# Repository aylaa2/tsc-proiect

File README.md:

# OpenBook – Open-Source E-Book Reader

OpenBook este un e-book reader open-source, low-cost, dezvoltat în cadrul proiectului TSC.  
Dispozitivul este construit pe baza microcontrolerului **ESP32-C6** și integrează funcționalități avansate de afișare, comunicație și consum redus de energie, fiind pregătit pentru producție în masă.

---

##  Diagrama Bloc

Diagrama bloc care ilustrează conexiunile dintre toate componentele:

---

##  BOM – Bill of Materials

# Bill of Materials (BOM)

| Package | Parts | Datasheet | 
|:--------|:------|:----------|
| ADAFRUIT_CHIP-LED0603 | CHG_LED | [Link](https://www.snapeda.com/parts/KP-1608SURCK/Kingbright/view-part/?ref=search&t=LED%200603) | 
| SJ | SJ1 | [Link](https://grabcad.com/library/solder-jumpers-1) |
| ESP32_WROVER_EAGLE-LTSPICE_R0402 | R1_PWRUSB, R1, R1_PINH1, R2-PINH, R2-PINH1, R5, R6, R7, R8, R9, R10, R_BOOT, R_CL1, R_RESET, R3, R1_PINH, R4, R_CHANGE, R_CAPACITOR, R2, R1_BAT, R2_BAT, R2_USB, R2_USB1 | [Link](https://componentsearchengine.com/part-view/R0402%201%25%20100%20K%20(RC0402FR-07100KL)/YAGEO) | 
| ESP32_WROVER_EAGLE-LTSPICE_C0402 | C1, C2, C4_USB, C6, C8, C9, C10, C_DELAY, EPD_C5, EPD_C1, EPD_C2, EPD_C6, EPD_C7, EPD_C8, EPD_C9, EPD_C10, EPD_C11, EPD_C12, C7, C5, C4, C1_BAT, C1_BAT1, C1_BAT2, C2_BAT, C5_USB | [Link](https://componentsearchengine.com/part-view/CC0402MRX5R5BB106/YAGEO) | 
| RCL_CT3528 | C3 | [Link](https://stud33302.autodesk360.com/g/shares/SH30dd5QT870c25f12fc6065d74bcaa3bf24) |
| 112ATAARR03ATTEND | J4 | [Link](Link) |
| ESP32_WROVER_SPARKFUN-DISCRETESEMI_SOT23-3 | Q1, Q2 | [Link](https://ro.mouser.com/ProductDetail/Microchip-Technology/MCP73831T-5ACI-OT?qs=hH%252BOa0VZEiAcgAcEkuamXg%3D%3D) |
| SOT95P280X125-5N | IC1 | [Link](https://componentsearchengine.com/part-view/BD5229G-TR/ROHM%20Semiconductor) |
| MYBUTTON | BOOT_BUTTON, CHANGE_BUTTON, RESET_BUTTON | [Link](https://industry.panasonic.com/global/en/products/control/switch/light-touch/number/evqpuj02k) |
| CAPCP3225X100N | C10_SUPERCAP | [Link](https://www.snapeda.com/parts/CPH3225A/Seiko+Instruments/view-part/?ref=eda) | 
| SOIC127P1032X265-16N | U3 | [Link](https://www.snapeda.com/parts/DS3231SN%23/Analog+Devices/view-part/?ref=eda) | 
| XCVR_ESP32-C6-WROOM-1-N8 | U2 | [Link](https://www.snapeda.com/parts/ESP32-C6-WROOM-1-N8/Espressif+Systems/view-part/?ref=eda) | 
| ESP32C6_VARISTOR_CT/CN1812 | PFMF.050.1 | [Link](Link) | 
| ESP32_WROVER_AVX---SD0805S020S1R0_AVX_SD0805S020S1R0_0 | D2, D7 | [Link](https://eu.mouser.com/ProductDetail/KYOCERA-AVX/SD0805S020S1R0?qs=jCA%252BPfw4LHbpkAoSnwrdjw%3D%3D) | 
| ESP32_WROVER_BME680_PSON80P300X300X100-8N | SENSOR2 | [Link](https://www.snapeda.com/parts/BME680/Bosch/view-part/?welcome=home) | 
| ESP32_WROVER_SPARKFUN-IC-POWER_SOT23-5 | U0 | [Link](Link) |
| FH34SRJ24S05SH99 | J1 | [Link](Link) | 
| SON50P200X200X80-9N | U4 | [Link](https://www.snapeda.com/parts/MAX17048G+T10/Analog+Devices/view-part/?ref=eda) | 
| SOD3716X135N | D3, D4, D5 | [Link](Lihttps://eu.mouser.com/ProductDetail/KYOCERA-AVX/SD0805S020S1R0?qs=jCA%252BPfw4LHbpkAoSnwrdjw%3D%3Dnk) | 
| DIOC1608X36N | D6, D8, D9, D10, D11, D12 | [Link](https://www.snapeda.com/parts/PGB1010603MR/Littelfuse/view-part/?ref=eda) | 
| JST04_1MM_RA | J3 | [Link](https://componentsearchengine.com/part-view/USB4110-GF-A/GCT%20(GLOBAL%20CONNECTOR%20TECHNOLOGY)) | 
| SAMACSYS_PARTS_USB4110GFA | J2 | [Link](https://componentsearchengine.com/part-view/USB4110-GF-A/GCT%20(GLOBAL%20CONNECTOR%20TECHNOLOGY)) | 
| SOT95P280X145-6N | D1 | [Link](https://www.snapeda.com/parts/USBLC6-2SC6Y/STMicroelectronics/view-part/?ref=eda) | 
| SON127P600X800X80-9N | U1 | [Link](https://www.snapeda.com/parts/W25Q512JVEIQ/Winbond+Electronics/view-part/?ref=eda) | 
| SOT95P280X120-5N | IC4 | [Link](https://www.snapeda.com/parts/W25Q512JVEIQ/Winbond+Electronics/view-part/?ref=eda) |

##  Descriere Hardware

OpenBook folosește următoarele module și componente:

- **ESP32-C6-WROOM-1-N8** – Microcontroller principal cu conectivitate WiFi 6, BLE și Zigbee.
- **W25Q512JVEIQ** – Memorie Flash SPI pentru stocarea datelor.
- **MAX17048** – Fuel Gauge pentru monitorizarea nivelului de încărcare a bateriei.
- **MCP73831** – Circuit de încărcare Li-Ion prin USB Type-C.
- **DS3231** – Ceas de timp real cu acuratețe ridicată.
- **BME680** – Senzor ambiental pentru calitatea aerului, temperatură și umiditate.
- **CPH3225A** – Supercapacitor pentru backup RTC.
- **USB4110-GF-A** – Conector USB Type-C pentru alimentare și comunicație.

**Specificații de comunicație și interfețe:**
- **I2C**: DS3231 (RTC), BME680 (senzor ambiental)
- **SPI**: W25Q512JVEIQ (memorie Flash externă)
- **I2C/SPI**: Ecran E-Paper
- **Fuel Gauge (MAX17048)**: comunicație prin I2C
- **USB**: Alimentare și încărcare prin MCP73831 + conector USB-C

**Calcul de consum de energie:**
- Dispozitivul intră în mod Deep Sleep ESP32 pentru a minimiza consumul (~20 µA).
- Fuel Gauge optimizează încărcarea/descărcarea bateriei pentru o autonomie maximă.

---

##  Pini ESP32-C6 

Mai jos este un rezumat al pinilor folosiți pe microcontroller, cu funcțiile și componenta asociată:

| GPIO  | Componentă         | Funcție                     |
|-------|--------------------|-----------------------------|
| EN    | Buton Reset        | Reset hardware              |
| IO0   | RTC                | INT_RTC (interupt RTC)      |
| IO1   | RTC                | 32KHz output                |
| IO2   | SD Card            | MISO                        |
| IO3   | E-paper Display    | EPD_BUSY                    |
| IO4   | SD Card            | SS_SD (chip select)         |
| IO5   | E-paper Display    | EPD_DC                      |
| IO6   | SPI Shared         | SCK                         |
| IO7   | SPI Shared         | MOSI                        |
| IO8   | GPIO               | Utilizare generica          |
| IO9   | Boot Button        | Mod programare              |
| IO10  | E-paper Display    | EPD_CS                      |
| IO11  | NOR Flash          | FLASH_CS                    |
| IO12  | USB Interface      | USB_D-                      |
| IO13  | USB Interface      | USB_D+                      |
| IO15  | Buton Change       | Detectare schimbare         |
| IO16  | UART               | TX (debug serial)           |
| IO17  | UART               | RX (debug serial)           |
| IO18  | RTC                | RTC_RST                     |
| IO19  | MAX17048           | I2C_PW (alimentare I2C)     |
| IO20  | E-paper Display    | EPD_3V3_C (power control)   |
| IO21  | I2C Shared         | SDA                         |
| IO22  | I2C Shared         | SCL                         |
| IO23  | E-paper Display    | EPD_RST                     |

---

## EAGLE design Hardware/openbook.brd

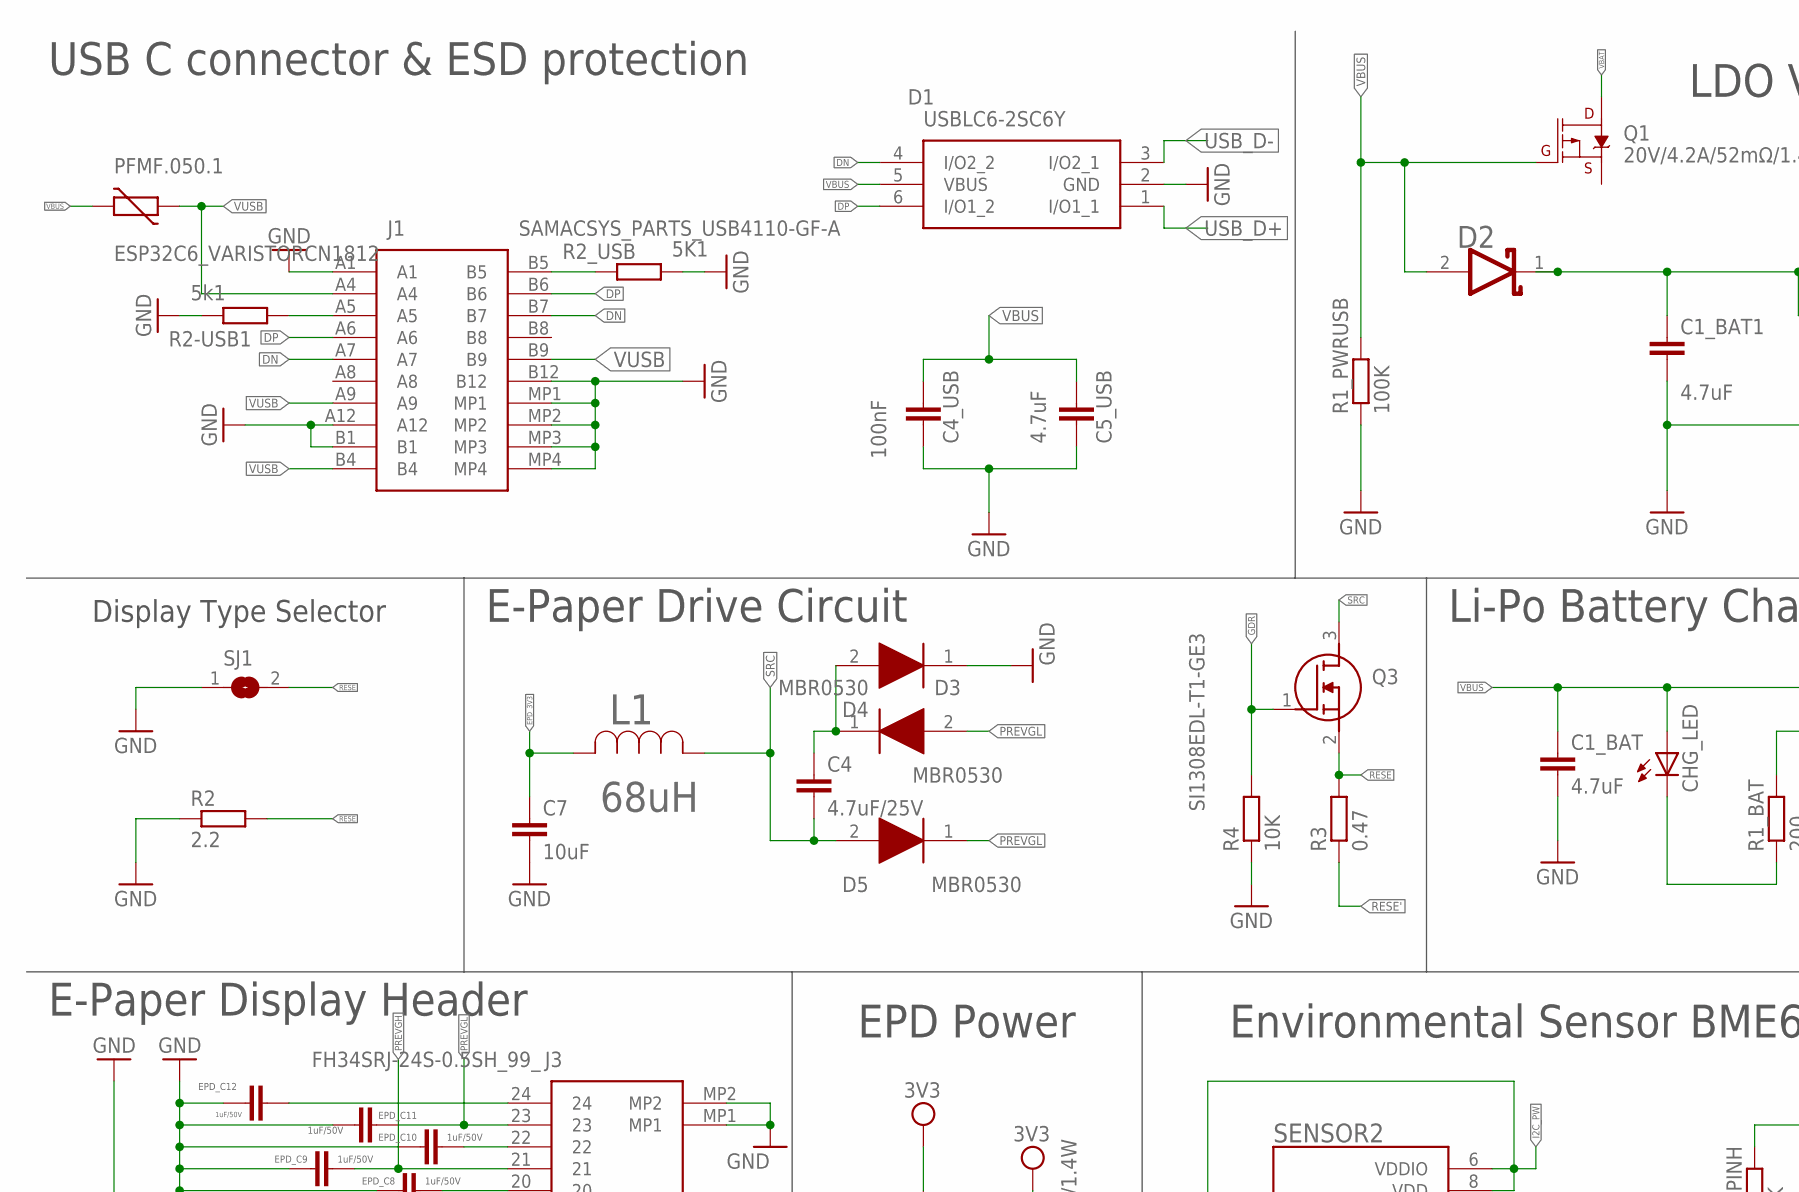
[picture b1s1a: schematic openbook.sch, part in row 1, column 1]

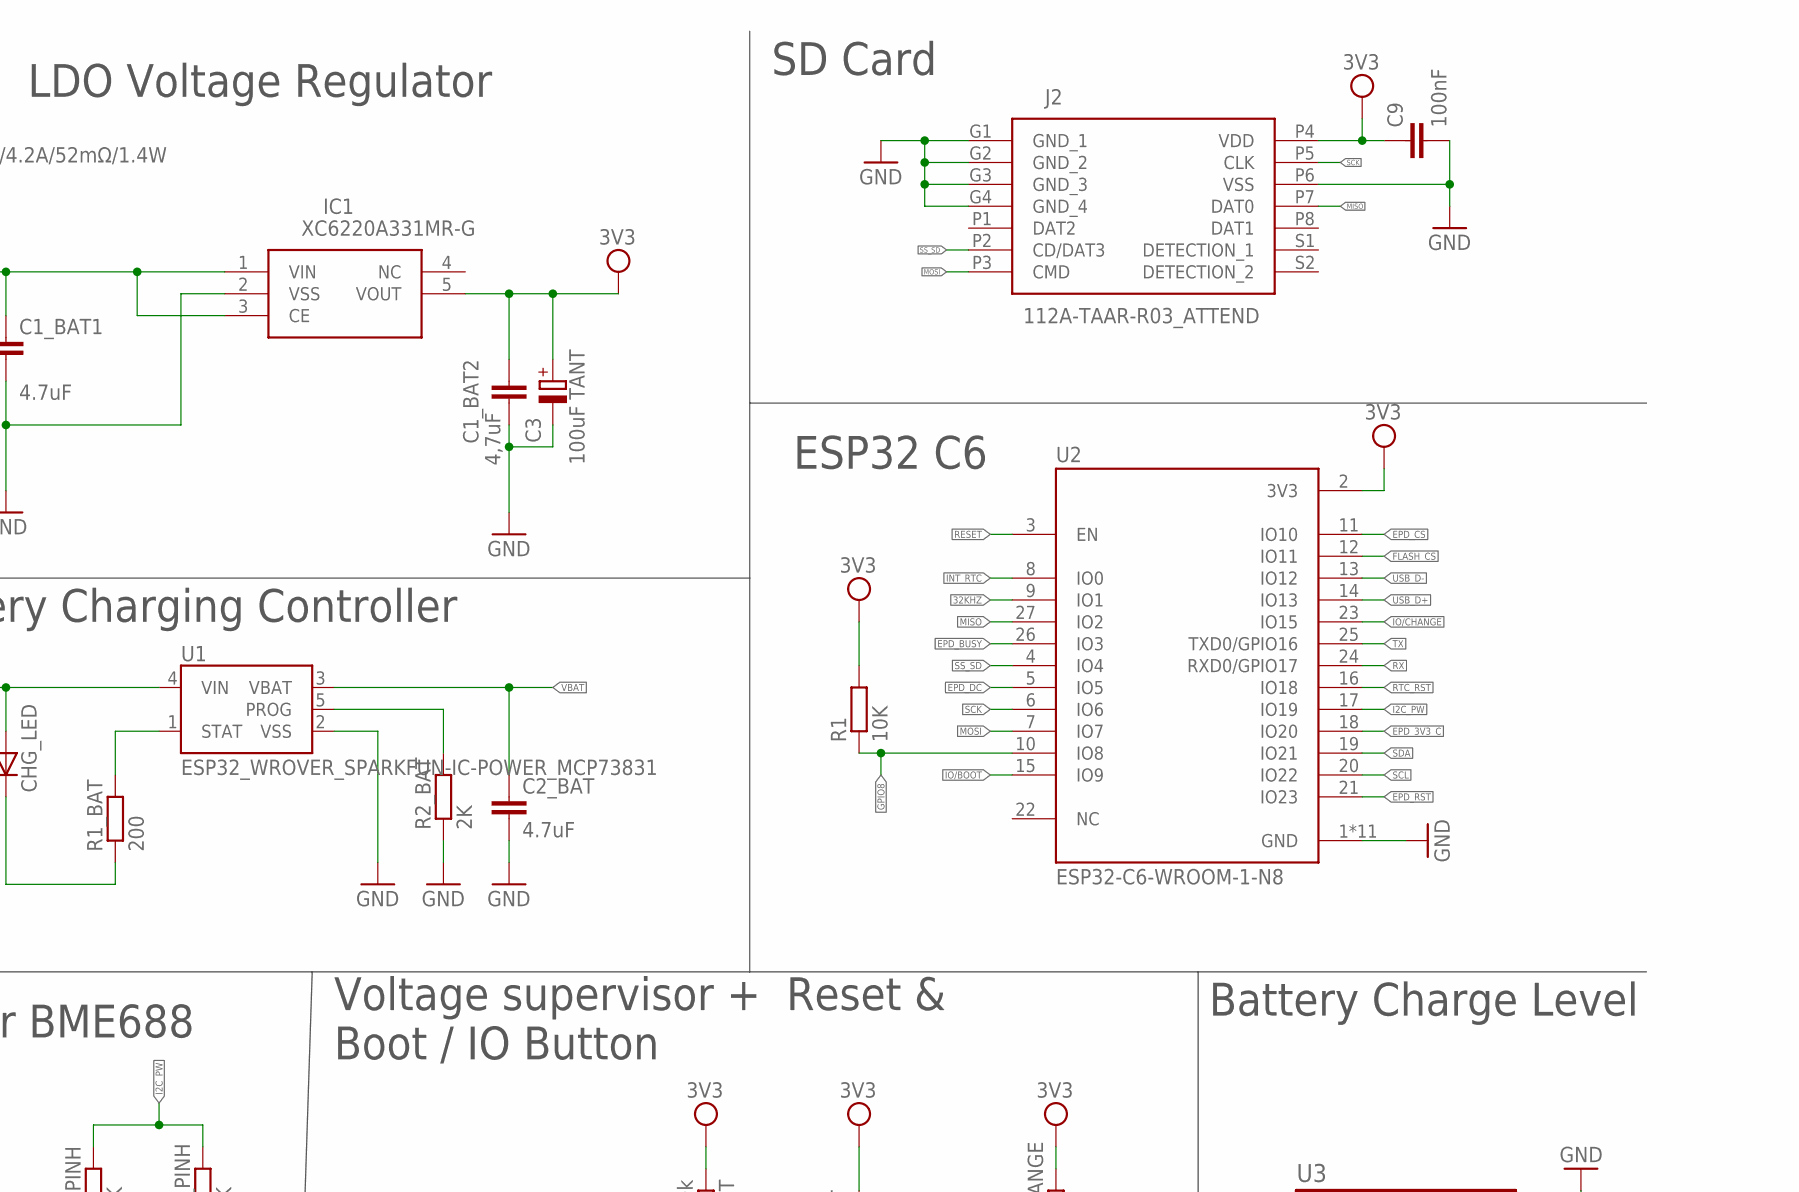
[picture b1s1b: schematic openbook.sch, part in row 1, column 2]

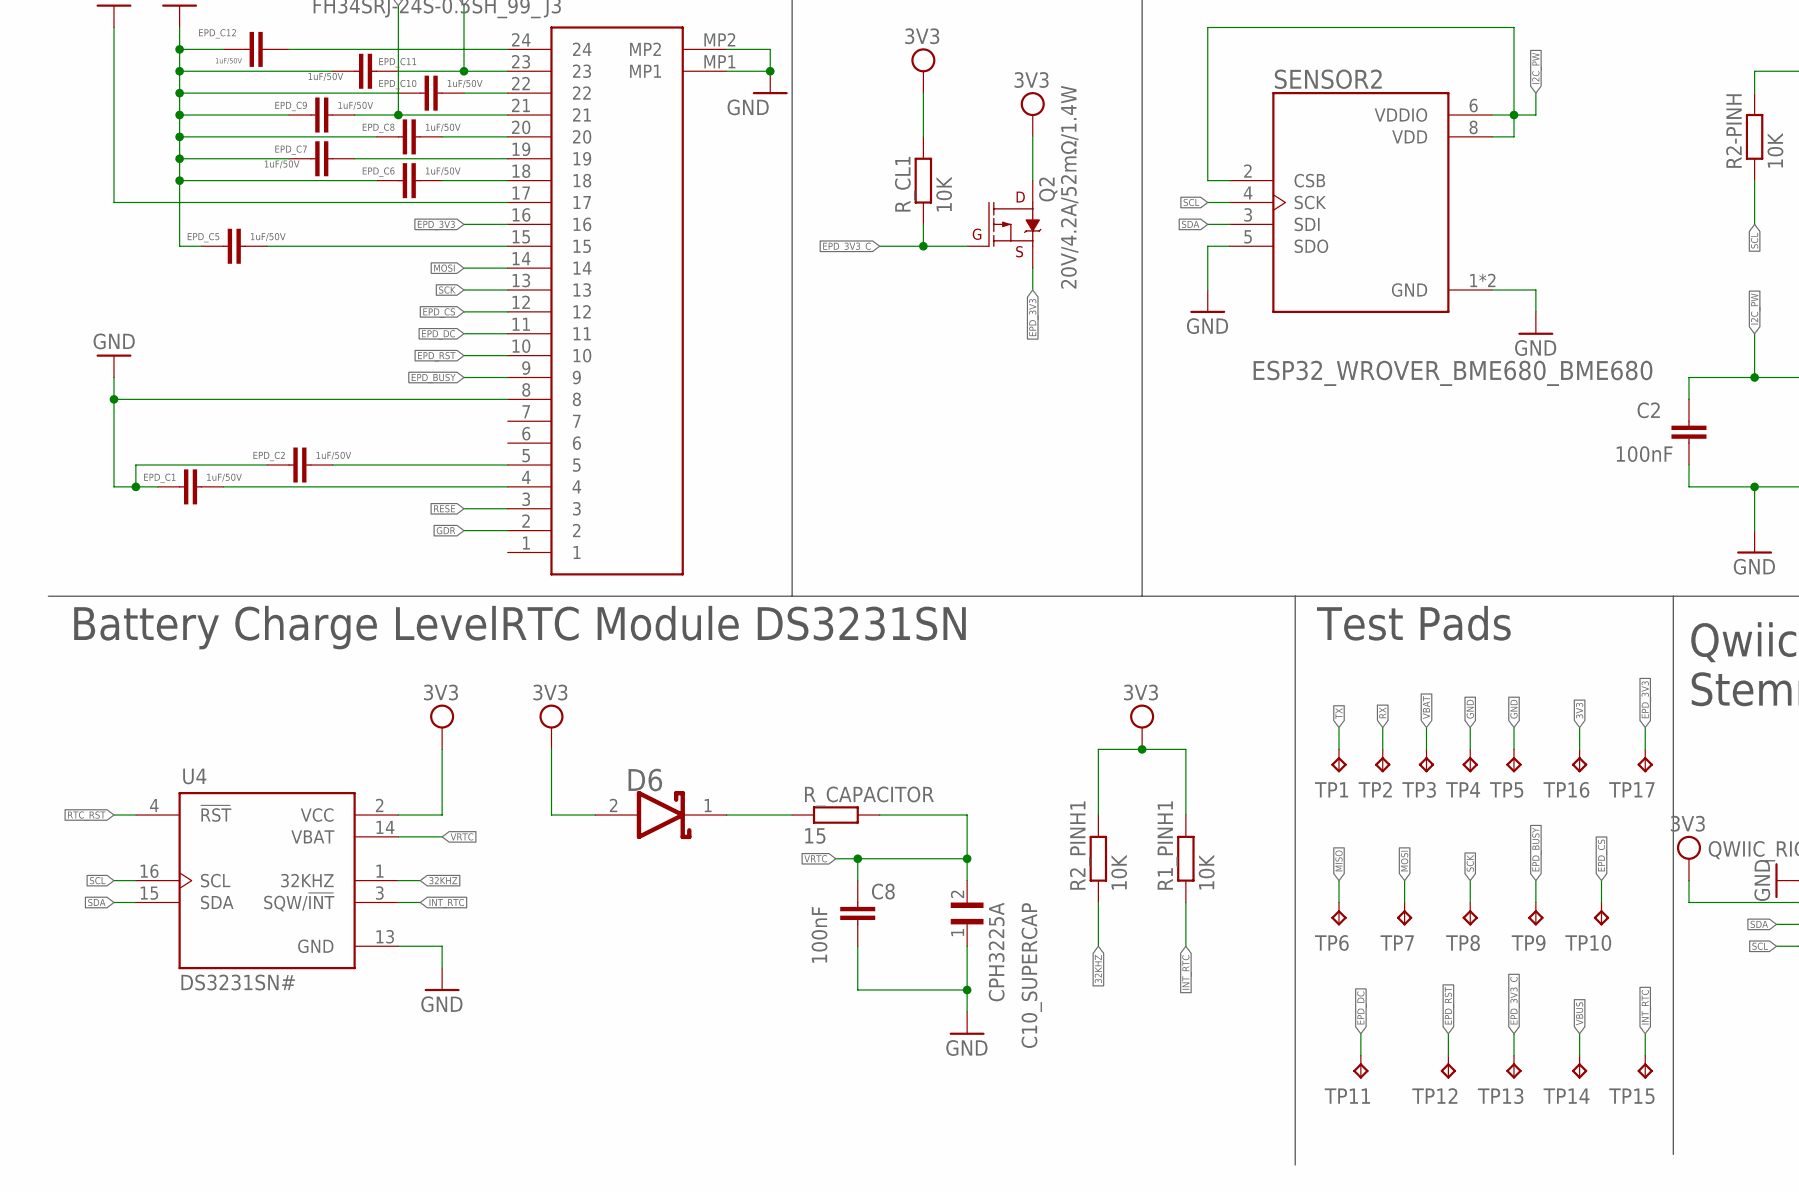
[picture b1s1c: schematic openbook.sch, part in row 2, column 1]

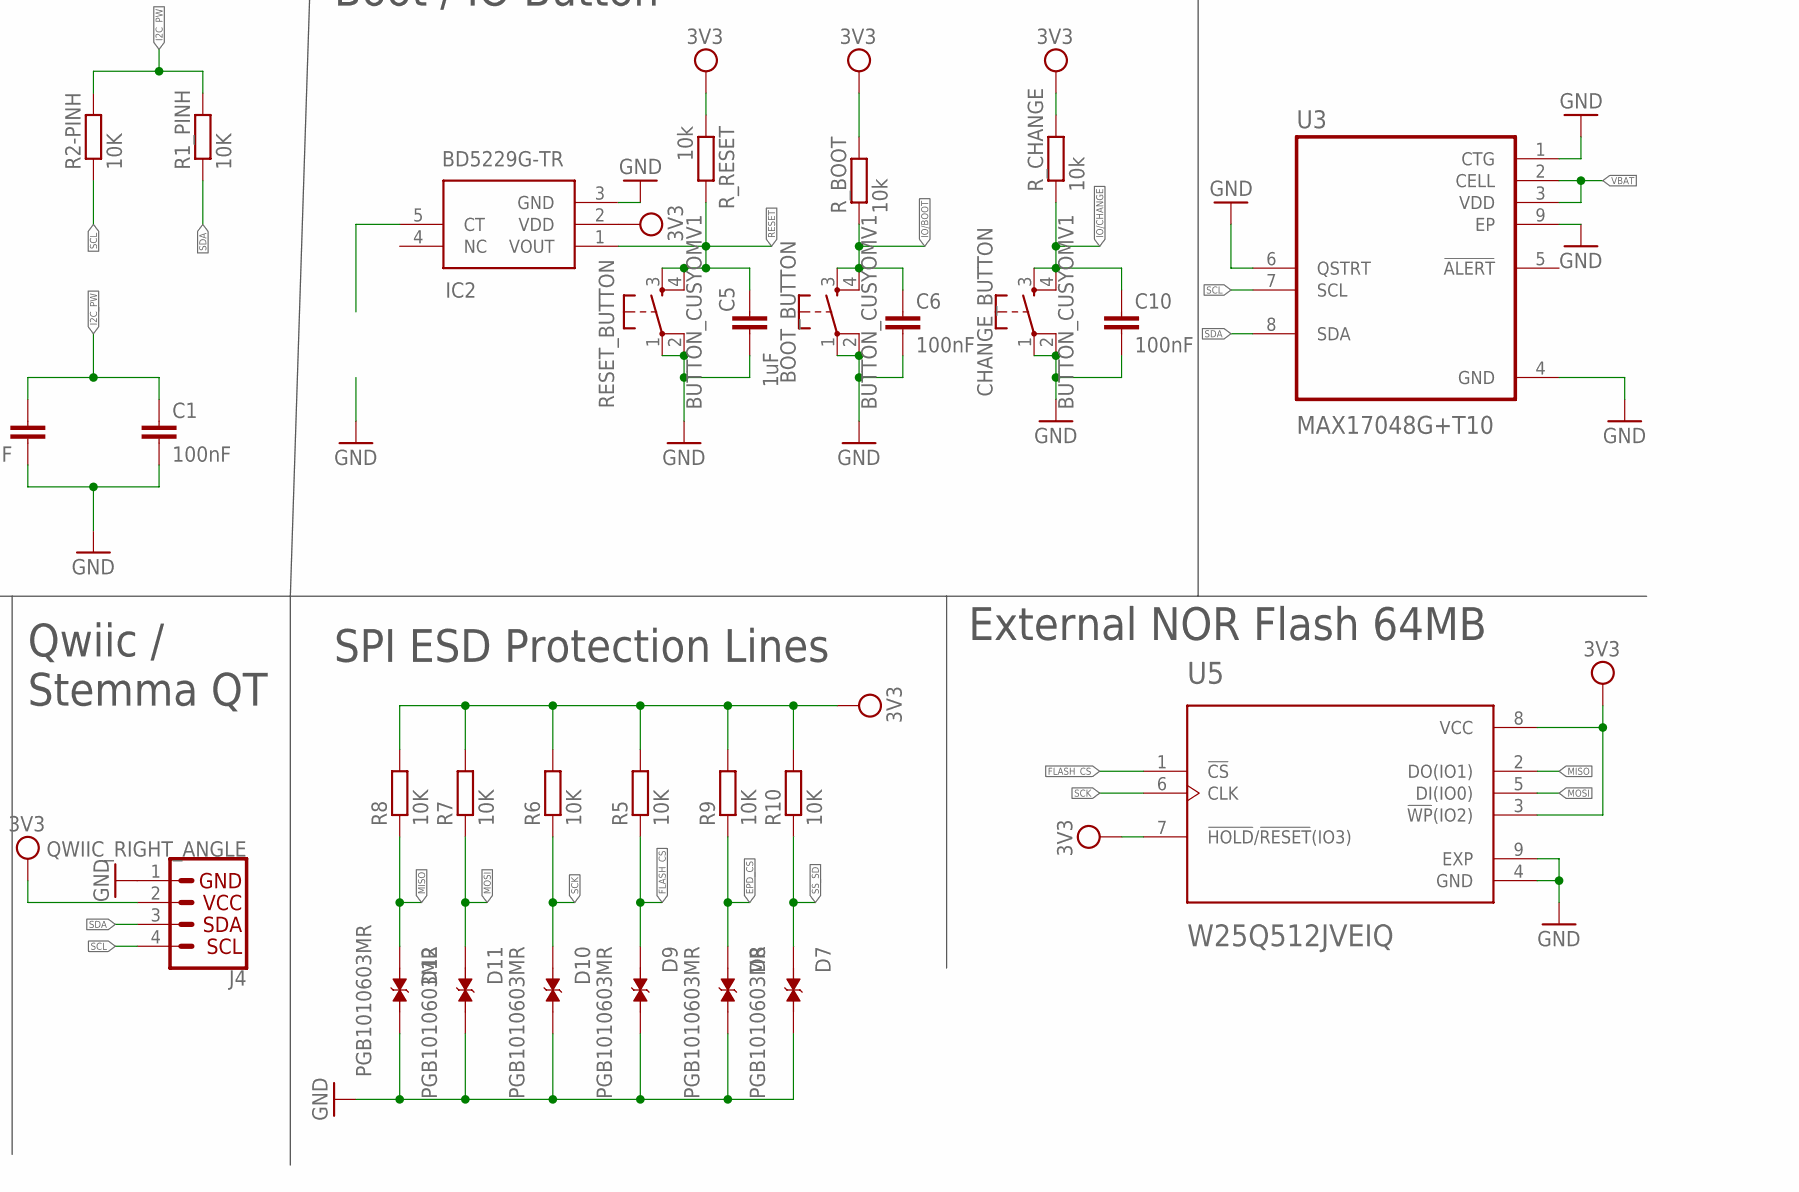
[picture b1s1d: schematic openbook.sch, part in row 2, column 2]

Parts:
BOOT_BUTTON: BUTTON_CUSYOMV1; MYBUTTON
C1, C2, C4_USB, C6, C8, C9, C10: 100nF; ESP32_WROVER_EAGLE-LTSPICE_C0402
C1_BAT, C1_BAT1, C2_BAT, C5_USB: 4.7uF; ESP32_WROVER_EAGLE-LTSPICE_C0402
C1_BAT2: 4,7uF; ESP32_WROVER_EAGLE-LTSPICE_C0402
C3: 100uF TANT; RCL_CT3528
C4: 4.7uF/25V; ESP32_WROVER_EAGLE-LTSPICE_C0402
C5: 1uF; ESP32_WROVER_EAGLE-LTSPICE_C0402
C7: 10uF; ESP32_WROVER_EAGLE-LTSPICE_C0402
C10_SUPERCAP: CPH3225A; CAPCP3225X100N
CHANGE_BUTTON: BUTTON_CUSYOMV1; MYBUTTON
CHG_LED: ADAFRUIT_LEDCHIP-LED0603; ADAFRUIT_CHIP-LED0603
D1: USBLC6-2SC6Y; SOT95P280X145-6N
D2, D6: ESP32_WROVER_AVX---SD0805S020S1R0_AVX_SD0805S020S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; SOT95P280X120-5N
D3, D4, D5: MBR0530; SOD3716X135N
D7, D8, D9, D10, D11, D12: PGB1010603MR; DIOC1608X36N
EPD_C1, EPD_C2, EPD_C5, EPD_C6, EPD_C7, EPD_C8, EPD_C9, EPD_C10, EPD_C11, EPD_C12: 1uF/50V; ESP32_WROVER_EAGLE-LTSPICE_C0402
IC1: XC6220A331MR-G; SOT95P280X120-5N
IC2: BD5229G-TR; SOT95P280X120-5N
J1: SAMACSYS_PARTS_USB4110-GF-A; SAMACSYS_PARTS_USB4110GFA
J2: 112A-TAAR-R03_ATTEND; 112ATAARR03ATTEND
J3: FH34SRJ-24S-0.5SH_99_; FH34SRJ24S05SH99
J4: QWIIC_RIGHT_ANGLE; JST04_1MM_RA
L1: 68uH; IND_4828-WE-TPC_WRE
PFMF.050.1: ESP32C6_VARISTORCN1812; ESP32C6_VARISTOR_CT/CN1812
Q1, Q2: 20V/4.2A/52mΩ/1.4W; ESP32_WROVER_SPARKFUN-IC-POWER_SOT23-5
Q3: SI1308EDL-T1-GE3; SOT65P210X110-3N
R1, R1_PINH, R1_PINH1, R2-PINH, R2_PINH1, R4, R5, R6, R7, R8, R9, R10: 10K; ESP32_WROVER_EAGLE-LTSPICE_R0402
R1_BAT: 200; ESP32_WROVER_EAGLE-LTSPICE_R0402
R1_PWRUSB: 100K; ESP32_WROVER_EAGLE-LTSPICE_R0402
R2: 2.2; ESP32_WROVER_EAGLE-LTSPICE_R0402
R2-USB1: 5k1; ESP32_WROVER_EAGLE-LTSPICE_R0402
R2_BAT: 2K; ESP32_WROVER_EAGLE-LTSPICE_R0402
R2_USB: 5K1; ESP32_WROVER_EAGLE-LTSPICE_R0402
R3: 0.47; ESP32_WROVER_EAGLE-LTSPICE_R0402
RESET_BUTTON: BUTTON_CUSYOMV1; MYBUTTON
R_BOOT: 10k; ESP32_WROVER_EAGLE-LTSPICE_R0402
R_CAPACITOR: 15; ESP32_WROVER_EAGLE-LTSPICE_R0402
R_CHANGE: 10k; ESP32_WROVER_EAGLE-LTSPICE_R0402
R_CL1: 10K; ESP32_WROVER_EAGLE-LTSPICE_R0402
R_RESET: 10k; ESP32_WROVER_EAGLE-LTSPICE_R0402
SENSOR2: ESP32_WROVER_BME680_BME680; ESP32_WROVER_BME680_PSON80P300X300X100-8N
SJ1: SJ
TP1, TP2, TP3, TP4, TP5, TP6, TP7, TP8, TP9, TP10, TP11, TP12, TP13, TP14, TP15, TP16, TP17: TPTP20R; TP20R
U1: ESP32_WROVER_SPARKFUN-IC-POWER_MCP73831; SOT95P280X125-5N
U2: ESP32-C6-WROOM-1-N8; XCVR_ESP32-C6-WROOM-1-N8
U3: MAX17048G+T10; SON50P200X200X80-9N
U4: DS3231SN#; SOIC127P1032X265-16N
U5: W25Q512JVEIQ; SON50P200X200X80-9N

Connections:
3V3: C1_BAT2.1, C3.+, C9.1, D6.2 (ANODE), IC1.5 (VOUT), IC2.2 (VDD), J2.P4 (VDD), J4.2, Q2.3 (D), R1.2, R1_PINH1.2, R2_PINH1.2, R5.2, R6.2, R7.2, R8.2, R9.2, R10.2, R_BOOT.2, R_CHANGE.2, R_CL1.2, R_RESET.1, TP16.TP, U2.2 (3V3), U4.2 (VCC), U5.3 (!WP!(IO2)), U5.7 (!HOLD!/!RESET!(IO3)), U5.8 (VCC)
32KHZ: R2_PINH1.1, U2.9 (IO1), U4.1 (32KHZ)
DN: D1.4 (I/O2_2), J1.A7, J1.B7
DP: D1.6 (I/O1_2), J1.A6, J1.B6
EPD_3V3: C7.1, J3.16, L1.2, Q2.2 (S), TP17.TP
EPD_3V3_C: Q2.1 (G), R_CL1.1, TP13.TP, U2.18 (IO20)
EPD_BUSY: J3.9, TP9.TP, U2.26 (IO3)
EPD_CS: D8.1, J3.12, R9.1, TP10.TP, U2.11 (IO10)
EPD_DC: J3.11, TP11.TP, U2.5 (IO5)
EPD_RST: J3.10, TP12.TP, U2.21 (IO23)
FLASH_CS: D9.1, R5.1, U2.12 (IO11), U5.1 (!CS)
GDR: J3.2, Q3.1 (G), R4.2
GND: BOOT_BUTTON.1, BOOT_BUTTON.2, C1.2, C1_BAT.2, C1_BAT1.2, C1_BAT2.2, C2.2, C2_BAT.2, C3.-, C4_USB.2, C5.2, C5_USB.2, C6.2, C7.2, C9.2, C10.2, CHANGE_BUTTON.1, CHANGE_BUTTON.2, D7.2, D8.2, D9.2, D10.2, D11.2, D12.2, EPD_C1.1, EPD_C2.1, EPD_C5.1, EPD_C6.1, EPD_C7.1, EPD_C8.1, EPD_C9.1, EPD_C10.1, EPD_C11.1, EPD_C12.1, IC1.2 (VSS), IC2.3 (GND), J1.A1, J1.A12, J1.B1, J1.B12, J1.MP1, J1.MP2, J1.MP3, J1.MP4, J2.G1 (GND_1), J2.G2 (GND_2), J2.G3 (GND_3), J2.G4 (GND_4), J2.P6 (VSS), J3.8, J3.17, J3.MP1, J3.MP2, J4.1, R1_PWRUSB.1, R2.1, R2-USB1.1, R2_BAT.1, R2_USB.2, R4.1, RESET_BUTTON.1, RESET_BUTTON.2, SENSOR2.1 (GND), SENSOR2.5 (SDO), SENSOR2.7 (GND), SJ1.1, TP4.TP, TP5.TP, U1.2 (VSS), U2.1 (GND), U2.28 (GND), U2.29_1 (GND), U2.29_2 (GND), U2.29_3 (GND), U2.29_4 (GND), U2.29_5 (GND), U2.29_6 (GND), U2.29_7 (GND), U2.29_8 (GND), U2.29_9 (GND), U3.1 (CTG), U3.4 (GND), U3.6 (QSTRT), U3.9 (EP), U4.13 (GND), U5.4 (GND), U5.9 (EXP)
GPIO8: R1.1, U2.10 (IO8)
I2C_PW: C1.1, C2.1, R1_PINH.2, R2-PINH.2, SENSOR2.2 (CSB), SENSOR2.6 (VDDIO), SENSOR2.8 (VDD), U2.17 (IO19)
INT_RTC: R1_PINH1.1, TP15.TP, U2.8 (IO0), U4.3 (SQW/!INT)
IO/BOOT: BOOT_BUTTON.3, BOOT_BUTTON.4, C6.1, R_BOOT.1, U2.15 (IO9)
IO/CHANGE: C10.1, CHANGE_BUTTON.3, CHANGE_BUTTON.4, R_CHANGE.1, U2.23 (IO15)
MISO: D12.1, J2.P7 (DAT0), R8.1, TP6.TP, U2.27 (IO2), U5.2 (DO(IO1))
MOSI: D11.1, J2.P3 (CMD), J3.14, R7.1, TP7.TP, U2.7 (IO7), U5.5 (DI(IO0))
unnamed: J1.B5, R2_USB.1
unnamed: C1_BAT1.1, D2.1 (CATHODE), IC1.1 (VIN), IC1.3 (CE)
unnamed: J1.A5, R2-USB1.2
unnamed: C4.1, D3.1 (K), D4.2 (A)
unnamed: R1_BAT.2, U1.1 (STAT)
unnamed: R2_BAT.2, U1.5 (PROG)
unnamed: EPD_C12.2, J3.24
unnamed: EPD_C2.2, J3.5
unnamed: CHG_LED.C, R1_BAT.1
unnamed: EPD_C10.2, J3.22
unnamed: EPD_C8.2, J3.20
unnamed: EPD_C7.2, J3.19
unnamed: EPD_C6.2, J3.18
unnamed: EPD_C5.2, J3.15
unnamed: D6.1 (CATHODE), R_CAPACITOR.1
unnamed: C8.2, C10_SUPERCAP.1
unnamed: EPD_C1.2, J3.4
PREVGH: EPD_C9.2, J3.21
PREVGL: D3.2 (A), D5.1 (K), EPD_C11.2, J3.23
RESE: J3.3, Q3.2 (S), R2.2, R3.2, SJ1.2
RESE': R3.1
RESET: C5.1, IC2.1 (VOUT), RESET_BUTTON.3, RESET_BUTTON.4, R_RESET.2, U2.3 (EN)
RTC_RST: U2.16 (IO18), U4.4 (!RST)
RX: TP2.TP, U2.24 (RXD0/GPIO17)
SCK: D10.1, J2.P5 (CLK), J3.13, R6.1, TP8.TP, U2.6 (IO6), U5.6 (CLK)
SCL: J4.4, R2-PINH.1, SENSOR2.4 (SCK), U2.20 (IO22), U3.7 (SCL), U4.16 (SCL)
SDA: J4.3, R1_PINH.1, SENSOR2.3 (SDI), U2.19 (IO21), U3.8 (SDA), U4.15 (SDA)
SRC: C4.2, D5.2 (A), L1.1, Q3.3 (D)
SS_SD: D7.1, J2.P2 (CD/DAT3), R10.1, U2.4 (IO4)
TX: TP1.TP, U2.25 (TXD0/GPIO16)
USB_D+: D1.1 (I/O1_1), U2.14 (IO13)
USB_D-: D1.3 (I/O2_1), U2.13 (IO12)
VBAT: C2_BAT.1, Q1.3 (D), TP3.TP, U1.3 (VBAT), U3.2 (CELL), U3.3 (VDD)
VBUS: C1_BAT.1, C4_USB.1, C5_USB.1, CHG_LED.A, D1.5 (VBUS), D2.2 (ANODE), PFMF.050.1.2, Q1.1 (G), R1_PWRUSB.2, TP14.TP, U1.4 (VIN)
VRTC: C8.1, C10_SUPERCAP.2, R_CAPACITOR.2, U4.14 (VBAT)
VUSB: J1.A4, J1.A9, J1.B4, J1.B9, PFMF.050.1.1

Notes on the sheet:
USB C connector & ESD protection
LDO Voltage Regulator
SD Card
Display Type Selector
E-Paper Drive Circuit
Li-Po Battery Charging Controller
ESP32 C6
E-Paper Display Header
EPD Power
Environmental Sensor BME688
Voltage supervisor + Reset & Boot / IO Button
Battery Charge Level
Battery Charge LevelRTC Module DS3231SN
Test Pads
Qwiic / Stemma QT
SPI ESD Protection Lines
External NOR Flash 64MB

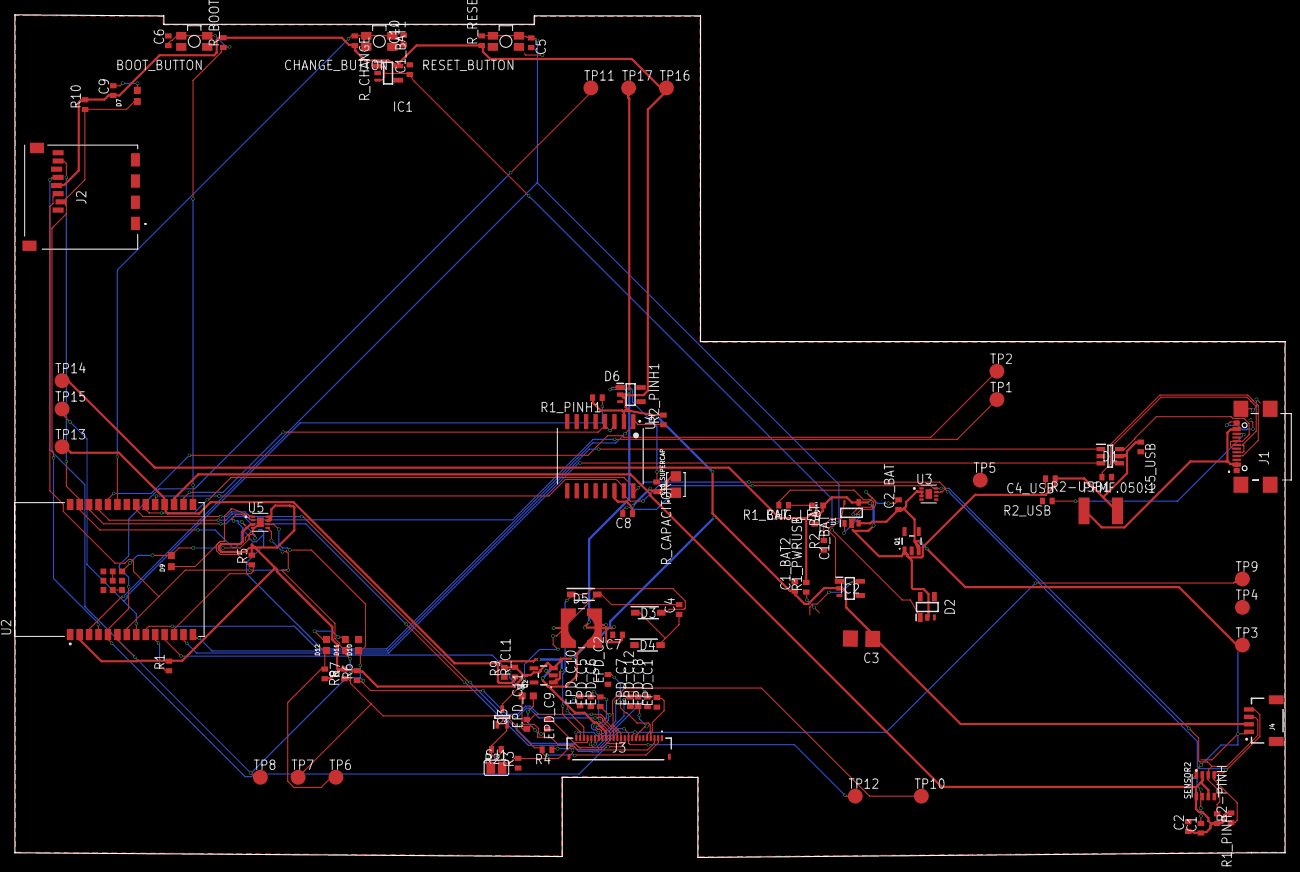
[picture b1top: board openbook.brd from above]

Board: 2 copper layers, 170.8 x 113.3 mm, 102 parts (0 on the bottom side), 55 nets.

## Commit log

2025-04-06 Create LICENSE
2025-04-06 Initial commit with OpenBook hardware files
2025-04-06 added readme.md
2025-04-06 added images
2025-04-06 animation
2025-04-06 animation 1
2025-04-06 final changes
2025-04-14 fixed readme
2025-04-14 fixed readme1
2025-04-15 fixed readme2
2025-04-15 fixed readme3
2025-04-15 updated pickandplace
2025-04-15 updated hardware
2025-04-15 updated 3d
2025-04-15 readme

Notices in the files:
parts and their libraries:
COPYRIGHT: Copyright (C) 2024 Ultra Librarian. All rights reserved.
